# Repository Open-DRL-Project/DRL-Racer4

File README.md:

<picture>
  <source media="(prefers-color-scheme: dark)" srcset="images/opendrl.svg">
  
</picture>

Custom firmware and tools for the DRL Racer4 developed by [@leszczy](https://github.com/hackrfstuff), [@Mr-milky-way](https://github.com/Mr-milky-way), [@ZionFPV](https://github.com/ZionFPV), [@MayanHawk](https://github.com/MayanHawk).

Firmware for the F4 and F7 flight controllers, EC and LED controllers, with Betaflight OSD, LED patterns and GIF uploads. Also supports replacement cameras, SmartAudio VTX control and CRSF receiver telemetry through the adapter.

* `configurator`: patches and assets for Betaflight Configurator 10.6.0.
* `firmware`: stock dumps, Betaflight patches, EC and LEDC source, and the Ghidra project.
* `flasher`: Windows application for identifying and flashing the boards.
* `hardware`: KiCad files for supporting boards.

Download the flasher, standalone firmware and Windows Configurator from [Releases](https://github.com/Open-DRL-Project/DRL-Racer4/releases/latest).

The [Firmware guide](firmware/README.md) covers building, editing and hardware specifications.

## Flashing

Update all three boards using the steps below. FC and EC depend on each other and must be updated together.

1. Download `DRL-Flasher` from [Releases](https://github.com/Open-DRL-Project/DRL-Racer4/releases/latest).
2. Extract the ZIP, then run `DRL Flasher.exe` from the extracted folder. Keep the other files and folders with it.
3. Select the latest build and choose `FC` as the first board to flash.
4. Press `Flash` and follow the instructions in the button. Click it again after completing each requested step, and wait for verification to finish.
5. Repeat for `EC`, then `LEDC`. The flashing order is FC, EC, LEDC.

Theoretically, the updated FC and EC could run with the original LEDC firmware, but most custom Betaflight LED functions would be unavailable. The original method of switching patterns by briefly shorting a pair of `USER` pads anywhere on the Racer4 would still work.

### FC and EC USB

With the Racer4's front facing away from you, the left micro USB port is Betaflight USB. The right port is EC USB.

### LEDC USB lead

The LEDC needs a separate lead for its USB JST socket. This connection does not power the board, so leave the LEDC seated in the PDB and connect battery power when the flasher asks.

With the board oriented as in the connection photos below, the first two socket contacts from the left are D- and D+. The fifth contact is ground. The lead needs these three signals.

You can use a BETAFPV SH1.0 adapter, or anything similar for 1S AIO boards. Its four-pin connector has the data pins in the middle, so the cable needs repinning at the adapter end.

1. Carefully lift the plastic retention tabs with tweezers to release the contacts. Remove the two wires on the right side, and move the remaining ones into the middle while keeping their order.
2. Solder a separate ground wire or hook probe lead to the adapter's `GND` pad. Leave `+5V` unconnected.
3. Insert the other four-pin plug into the left side of the LEDC's five-pin USB socket, as shown below. Leave the fifth socket position free.
4. Connect the separate ground lead to the right `USER` pad shown in the bottom-left photo. Alternatively, use pin 4, GND, of the W25Q64JVSSIQ flash chip, shown in the bottom-right photo.

## License

Project code and modifications are licensed under [GNU AGPLv3](LICENSE). Upstream code and bundled components retain their existing licenses. See [NOTICE](NOTICE) for the scope and third-party notices.

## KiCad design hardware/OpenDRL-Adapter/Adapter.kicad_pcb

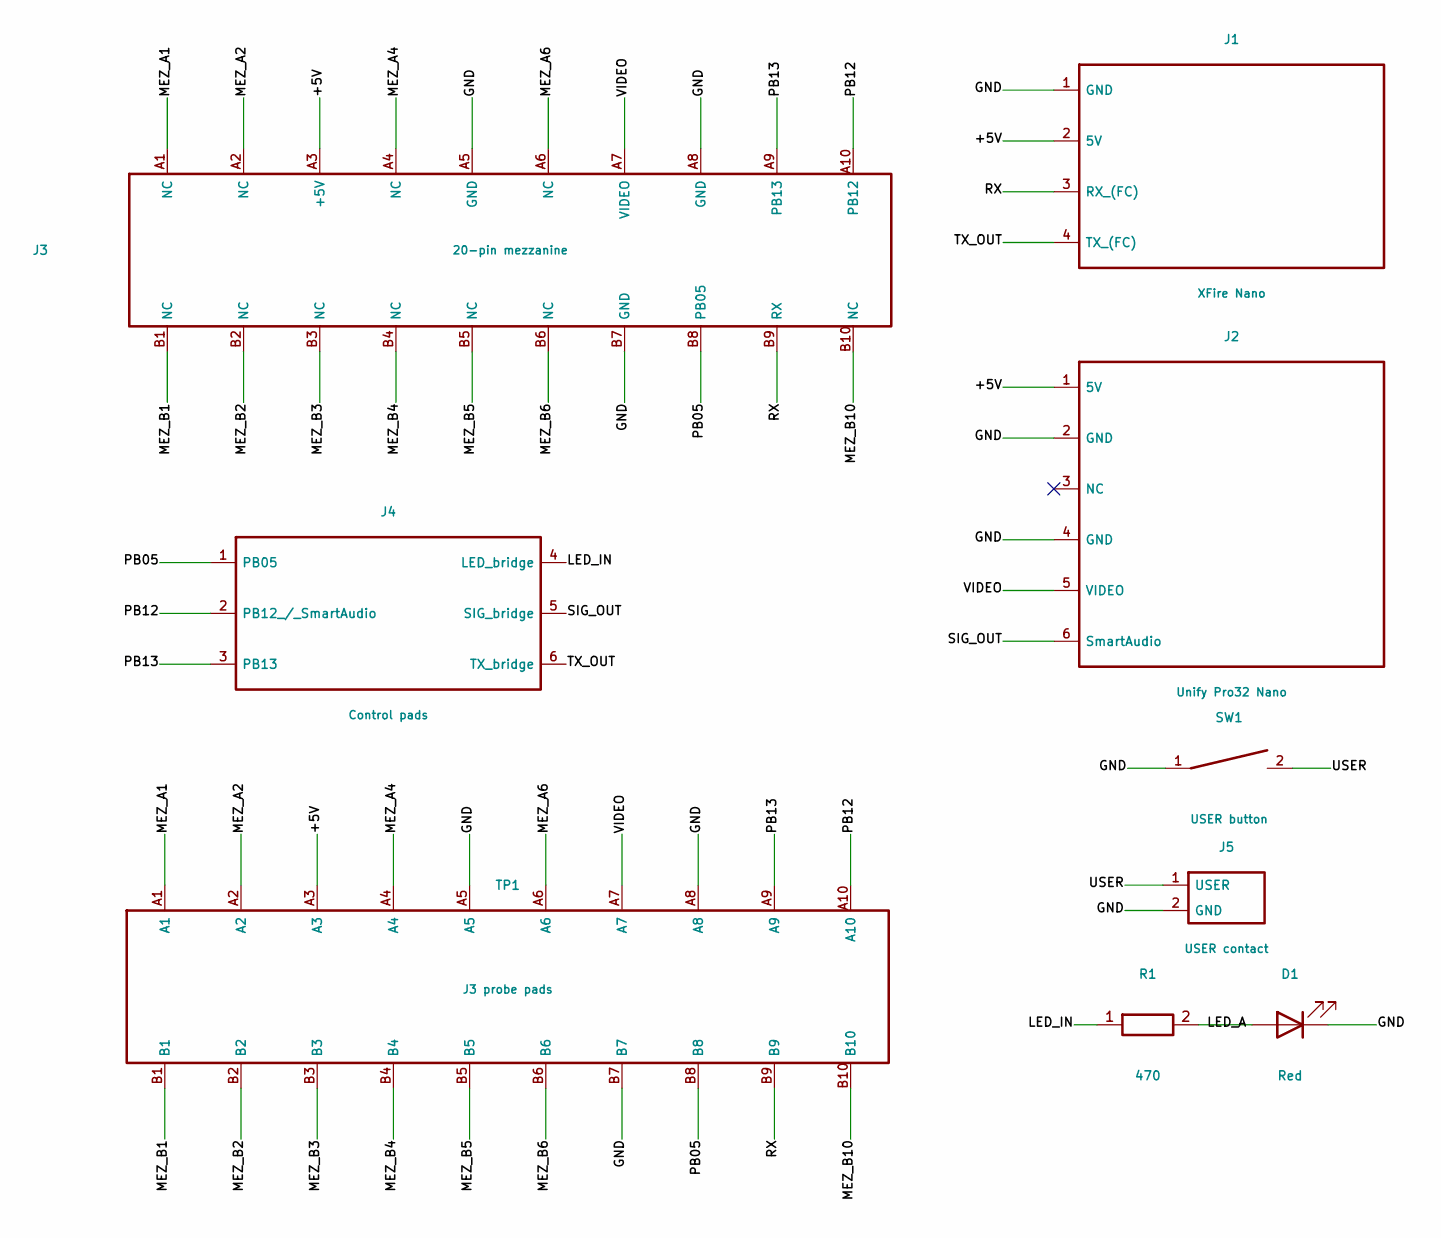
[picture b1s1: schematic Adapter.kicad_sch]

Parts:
D1: Red; LED_0402; MPN XL-1005SURC; LCSC C25503345
J1: XFire Nano; Header_4pin
J2: Unify Pro32 Nano; Header_6pin
J3: 20-pin mezzanine; DF12
J4: Control pads; Control
J5: USER contact; User
R1: 470; R_0402; MPN 0402WGF4700TCE; LCSC C25117
SW1: USER button; Button
TP1: J3 probe pads; TestPads

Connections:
/+5V: J1.2 (5V), J2.1 (5V), J3.A3 (+5V), TP1.A3
/GND: D1.1 (K), J1.1 (GND), J2.2 (GND), J2.4 (GND), J3.A5 (GND), J3.A8 (GND), J3.B7 (GND), J5.2 (GND), SW1.1, TP1.A5, TP1.A8, TP1.B7
/LED_A: D1.2 (A), R1.2
/LED_IN: J4.4 (LED bridge), R1.1
/MEZ_A1: J3.A1 (NC), TP1.A1
/MEZ_A2: J3.A2 (NC), TP1.A2
/MEZ_A4: J3.A4 (NC), TP1.A4
/MEZ_A6: J3.A6 (NC), TP1.A6
/MEZ_B1: J3.B1 (NC), TP1.B1
/MEZ_B2: J3.B2 (NC), TP1.B2
/MEZ_B3: J3.B3 (NC), TP1.B3
/MEZ_B4: J3.B4 (NC), TP1.B4
/MEZ_B5: J3.B5 (NC), TP1.B5
/MEZ_B6: J3.B6 (NC), TP1.B6
/MEZ_B10: J3.B10 (NC), TP1.B10
/PB05: J3.B8 (PB05), J4.1 (PB05), TP1.B8 (PB05)
/PB12: J3.A10 (PB12), J4.2 (PB12_/_SmartAudio), TP1.A10
/PB13: J3.A9 (PB13), J4.3 (PB13), TP1.A9
/RX: J1.3 (RX_(FC)), J3.B9 (RX), TP1.B9
/SIG_OUT: J2.6 (SmartAudio), J4.5 (SIG bridge)
/TX_OUT: J1.4 (TX_(FC)), J4.6 (TX bridge)
/USER: J5.1 (USER), SW1.2
/VIDEO: J2.5 (VIDEO), J3.A7 (VIDEO), TP1.A7

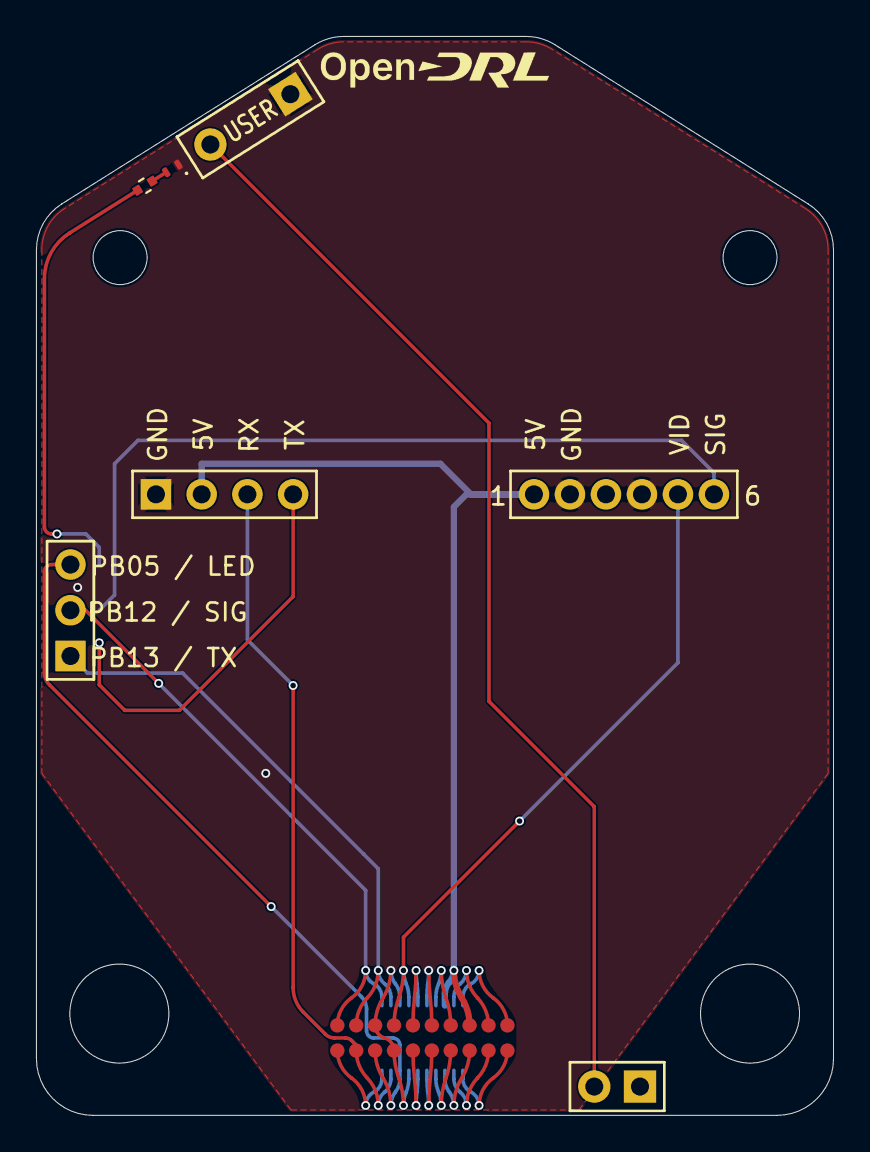
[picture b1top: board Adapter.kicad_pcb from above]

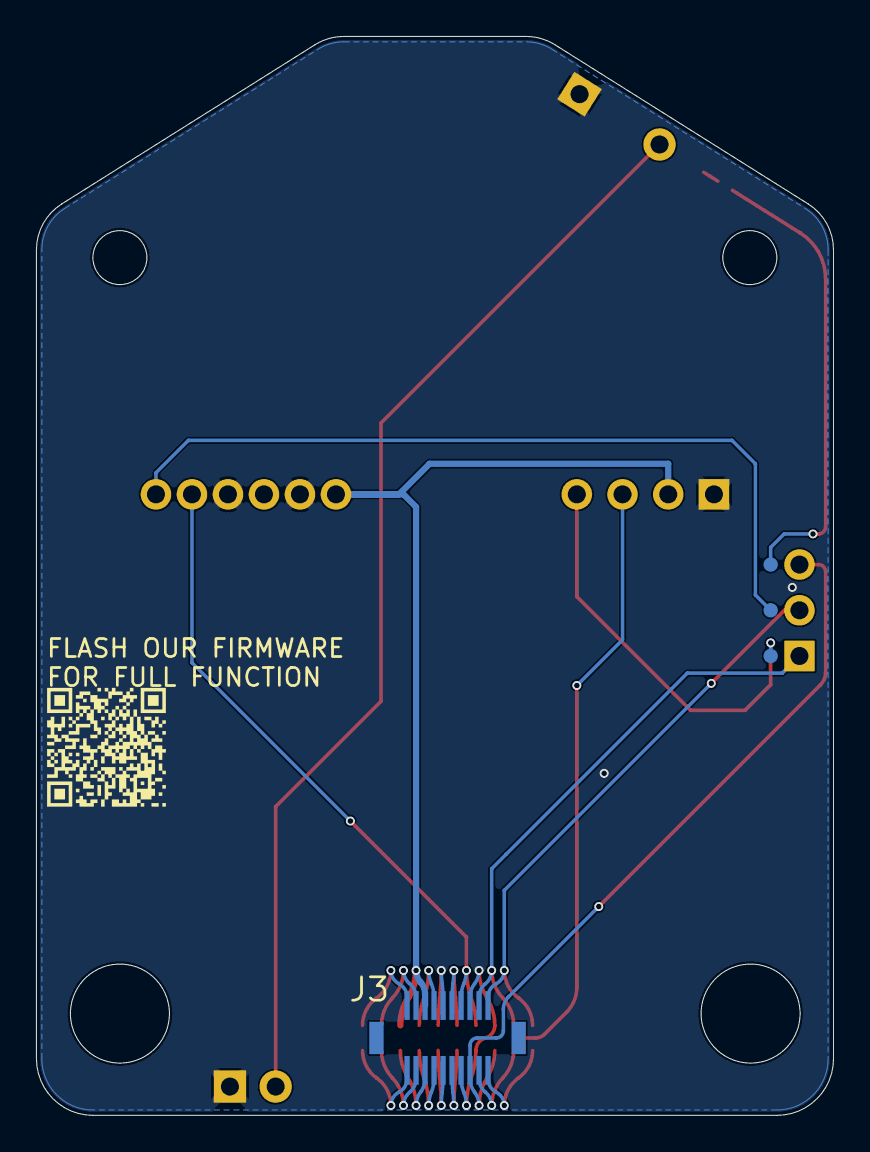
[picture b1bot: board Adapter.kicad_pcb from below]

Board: 2 copper layers, 44.3 x 59.9 mm, 15 parts (2 on the bottom side), 23 nets.

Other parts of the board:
H1, H2: 5.5mm; Hole_5.5mm
H3, H4: Hole_3mm
LOGO1: OpenDRL
QR1: QR
